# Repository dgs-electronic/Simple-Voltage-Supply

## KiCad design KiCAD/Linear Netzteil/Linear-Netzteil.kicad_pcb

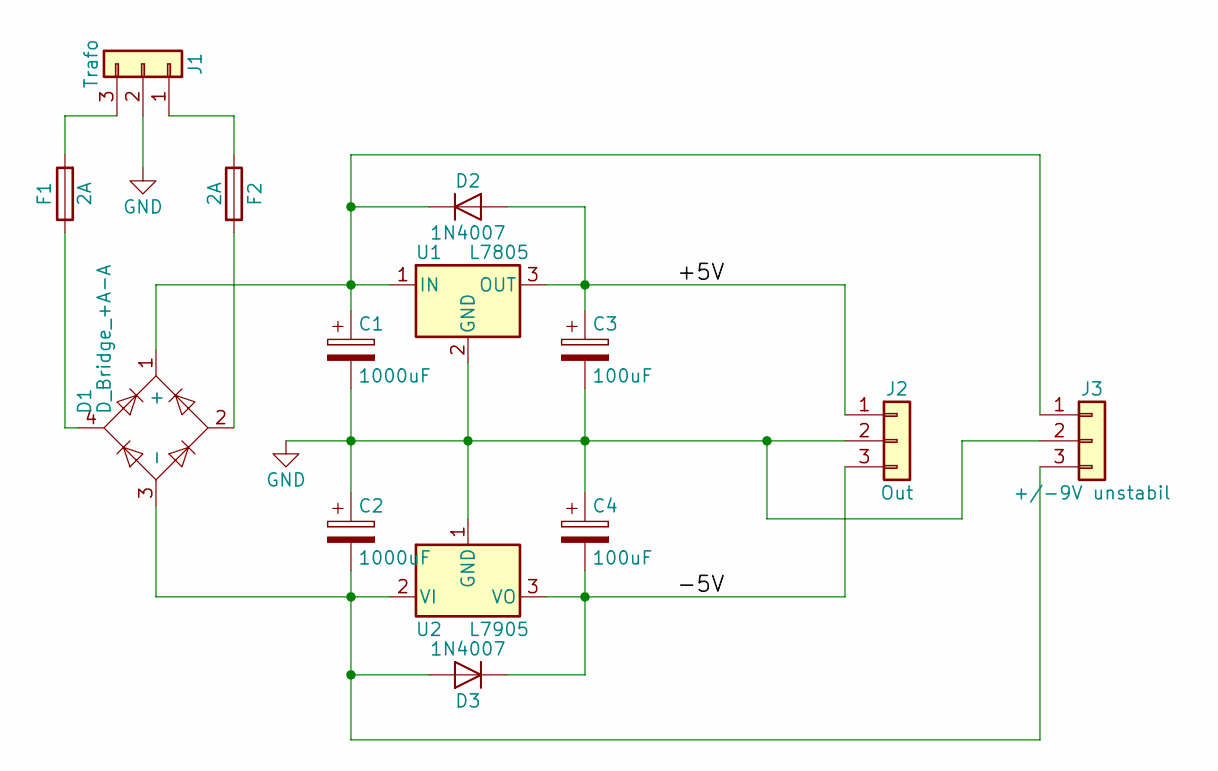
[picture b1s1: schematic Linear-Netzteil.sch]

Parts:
C1, C2: 1000uF; CP_Radial_D16.0mm_P7.50mm
C3, C4: 100uF; CP_Radial_D10.0mm_P5.00mm
D1: D_Bridge_+A-A; Diode_Bridge_Round_D8.9mm
D2, D3: 1N4007; D_DO-41_SOD81_P10.16mm_Horizontal
F1, F2: 2A; Fuseholder5x20_vert_closed_Bulgin_FX0456
J1: Trafo; PhoenixContact_GMSTBA-G_03x7.50mm_Angled
J2: Out; PhoenixContact_GMSTBA-G_03x7.50mm_Angled
J3: +/-9V unstabil; PhoenixContact_GMSTBA-G_03x7.50mm_Angled
U1: L7805; TO-220-3_Horizontal
U2: L7905; TO-220-3_Horizontal

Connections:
/+5V: C3.1, D2.2 (A), J2.1, U1.3 (OUT)
/-5V: C4.2, D3.1 (K), J2.3, U2.3 (VO)
GND: C1.2, C2.1, C3.2, C4.1, J1.2, J2.2, J3.2, U1.2 (GND), U2.1 (GND)
unnamed: C1.1, D1.1 (+), D2.1 (K), J3.1, U1.1 (IN)
unnamed: C2.2, D1.3 (-), D3.2 (A), J3.3, U2.2 (VI)
unnamed: D1.2, F2.2
unnamed: D1.4, F1.1
unnamed: F1.2, J1.3
unnamed: F2.1, J1.1

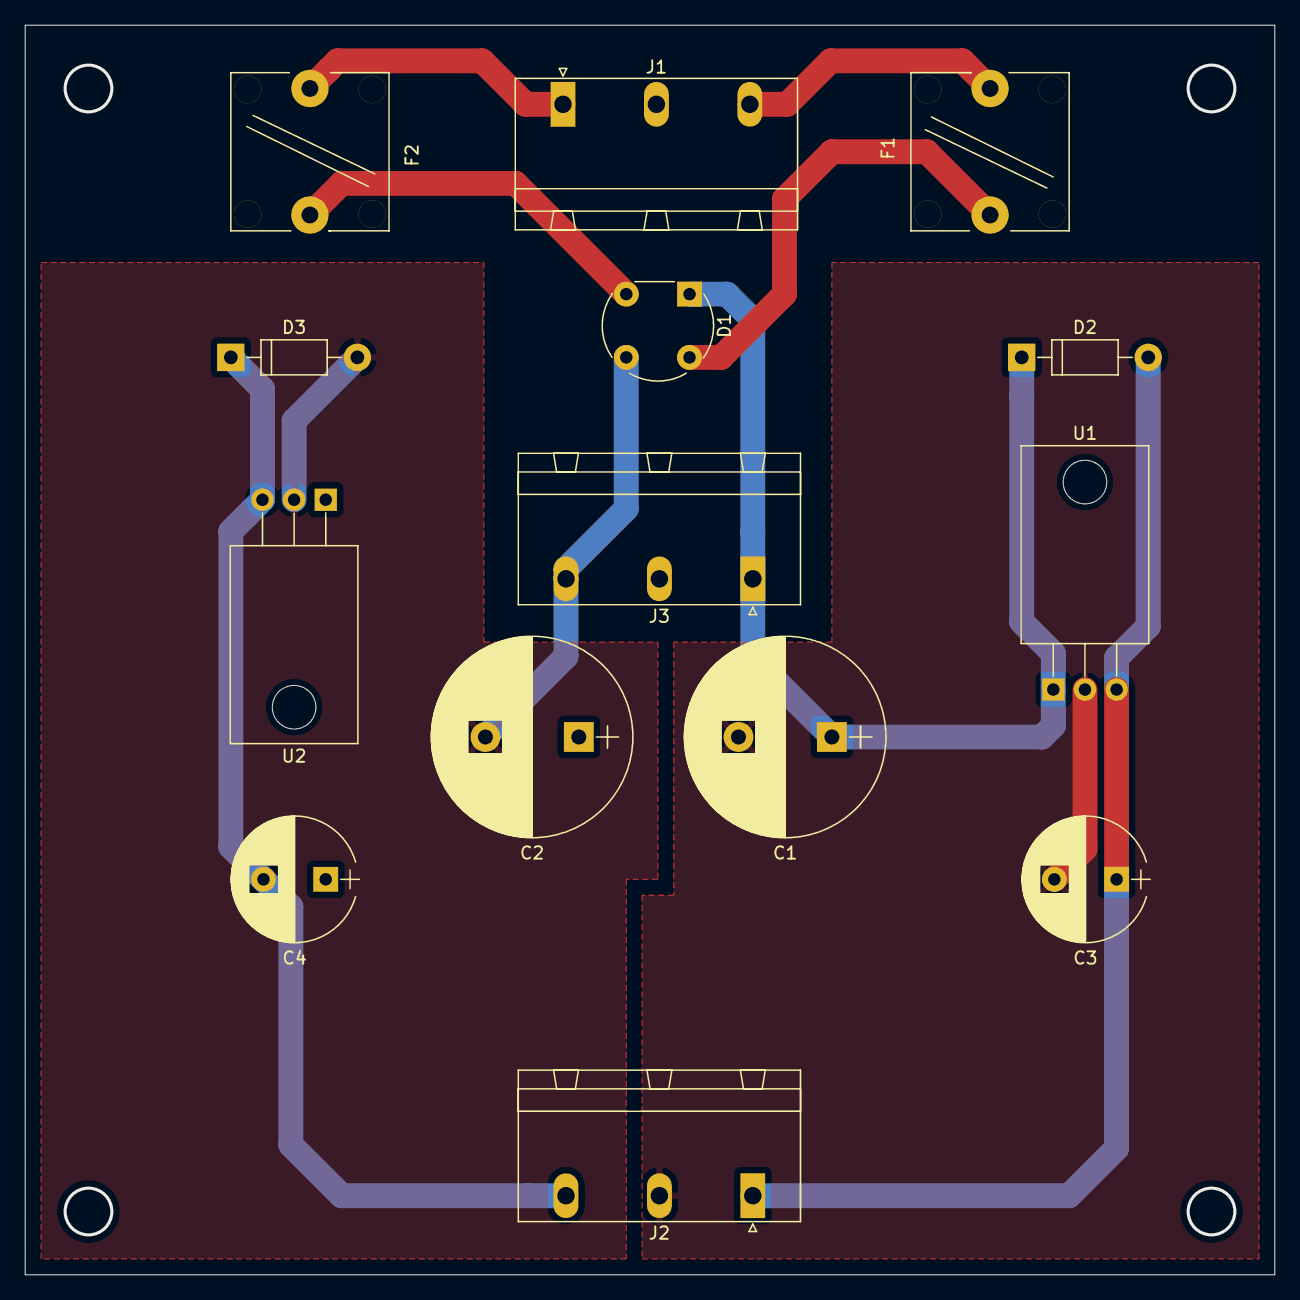
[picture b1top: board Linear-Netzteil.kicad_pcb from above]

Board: 2 copper layers, 100.3 x 100.3 mm, 14 parts (0 on the bottom side), 9 nets.

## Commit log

2019-11-02 Easy to use Voltage supply for Digital and Analog circuits
